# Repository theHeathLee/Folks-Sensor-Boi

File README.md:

# Folks Sensor Boi

> Multi-sensor engine telemetry unit for gasoline vehicles. Collects six engine parameters and transmits them wirelessly to a companion app and over CAN bus.

---

## Overview

A compact, sealed sensor interface box designed to mount in the engine bay of a classic or modified gasoline vehicle. Built around the ESP32-WROOM-S3.

Designed for JLCPCB fabrication and SMT assembly. 

---

## Features

| Channel | Sensor / method | Interface |
|---|---|---|
| Exhaust / CHT temperature | K-type thermocouple (galvanically isolated) | SPI — MAX31856 |
| Engine RPM | Ignition coil primary (optocoupled) | GPIO interrupt |
| Wheel speed | Hall effect sensor + Schmitt trigger | GPIO interrupt |
| Oil temperature | NTC sender (VDO-type) | ADC |
| Manifold vacuum / MAP | MPXHZ6115A6T1 15–115 kPa | ADC |
| Battery voltage | Resistor divider | ADC |

**Outputs**
- WiFi 802.11 b/g/n (AP mode) + BLE 4.2 → companion app
- CAN 2.0B @ 500 kbit/s via SN65HVD230

**Programming**
- USB-C (CP2102N) with auto-reset circuit — no manual BOOT/EN required

---

## Schematic

<!-- schematic-start -->

<!-- schematic-end -->

---

## Hardware

### MCU
- **ESP32-WROOM-32U-N4** — dual-core 240 MHz, WiFi, BLE, TWAI CAN, SPI, 12-bit ADC
- External u.FL antenna for full-vehicle wireless range

---
)

```
├── hardware/
│   ├── engine-sensor-box.kicad_pro
│   ├── engine-sensor-box.kicad_sch
│   ├── engine-sensor-box.kicad_pcb
│   ├── sym-lib-table
│   ├── fp-lib-table
│   └── jlcimport/               # project-local imported symbols + footprints
├── production/
│   ├── gerbers/
│   ├── bom.csv                  # JLCPCB-format BOM
│   └── positions.csv            # CPL file
├── docs/
│   └── engine_sensor_box_BOM.xlsx
└── README.md
```

---

## BOM

<!-- bom-start -->

[Open interactive BOM →](https://theheathlee.github.io/Folks-Sensor-Boi/bom.html)
<!-- bom-end -->

Full BOM with LCSC part numbers, stock status, unit costs, and placement tracking is in [`engine_sensor_box_BOM.xlsx`](engine_sensor_box_BOM.xlsx).

---

## Firmware

> Firmware repository: _link TBD_

---

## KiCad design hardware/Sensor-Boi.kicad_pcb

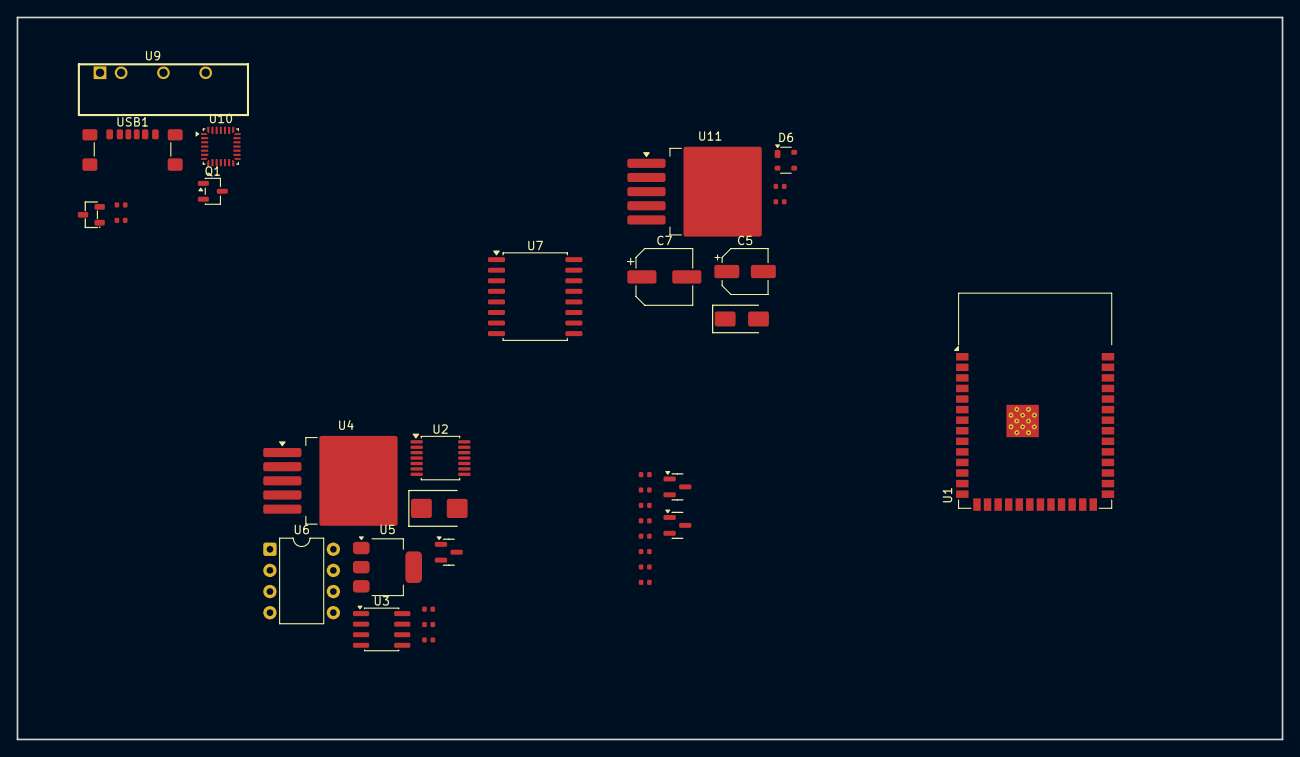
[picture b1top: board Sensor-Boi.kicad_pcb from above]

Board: 2 copper layers, 152.0 x 86.8 mm, 36 parts (0 on the bottom side), 19 nets, no tracks yet.

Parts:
C1, C2, C3, C4, C6: 100nF; C_0402
C5: 47uF 16V; CP_Elec_5x5.4
C7: 100uF 50V; CP_Elec_6.3x7.7
D1: BZX84C5V1; D_SOT-23
D2: SMBJ15A; D_SMB
D2#2: SS34; D_SMA
D3, D4: BZX84C3V3; D_SOT-23
D6: PRTR5V0U2X; SOT-143
Q1: 2N7002; SOT-23-3
R1: 100kΩ; R_0402
R2: 470Ω; R_0402
R3: 120Ω; R_0402
R4: 5.1kΩ; R_0402
R5, R10: 100Ω; R_0402
R6, R8: 10kΩ; R_0402
R7: 15kΩ; R_0402
R9: 180Ω; R_0402
U1: ESP32-S3-WROOM-1
U2: MAX31856; TSSOP-14_4.4x5mm_P0.65mm
U3: SN65HVD230; SOIC-8_3.9x4.9mm_P1.27mm
U4: LM2596S-5; TO-263-5_TabPin3
U5: AMS1117-3.3; SOT-223-3_TabPin2
U6: 6N137; DIP-8_W7.62mm
U7: ISO7741DWR; SOIC-16W_7.5x10.3mm_P1.27mm
U8: LTC4412ES6_TRPBF; SOT-23-3_L2.9-W1.3-P0.95-LS2.4-BR
U9: B0505LS-1WR3_C7465180
U10: CP2102N-A02-GQFN24R; QFN-28_4x4mm_P0.5mm
U11: LM2596S-3.3; TO-263-5_TabPin3
USB1: USB4085-GF-A_C7095263; USB_C_Receptacle_GCT_USB4135-GF-A_6P_TopMnt_Horizontal

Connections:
/3V3: C5.1, D6.4 (VCC), R9.2, U1.2 (3V3), U3.3 (VCC), U5.2 (VO), U7.16 (VCC2), U9.1 (VIN), U11.4 (FB)
/3V3_Isolated: U2.5 (AVDD), U2.8 (DVDD), U7.1 (VCC1), U9.6 (+Vo)
/12V: C7.1, U11.1 (VIN)
/CAN_H: R3.1, U3.7 (CANH)
/CAN_L: R3.2, U3.6 (CANL)
/CAN_RX: U1.10 (IO17), U3.4 (R)
/CAN_TX: U1.11 (IO18), U3.1 (D)
/Hall_Sensor: C6.1, R10.1
/Lambda_MCU: C2.1, D3.1, R6.2, R7.1, U1.6 (IO6)
/MAP_Signal_MCU: C3.1, D4.1, R8.2, U1.39 (IO1)
/OIL_MCU: C4.1, R9.1, U1.38 (IO2)
/TEMP_SCK: U2.10 (SCK), U7.3 (INA)
/TEMP_SDI: U2.12 (SDI), U7.5 (INC)
/TEMP_SDO: U2.11 (SDO), U7.4 (INB)
GND: C2.2, C3.2, C4.2, C5.2, C7.2, D2#2.1, D4.3, D6.1 (GND), R7.2, U1.1 (GND), U1.40 (GND), U1.41 (GND), U3.2 (GND), U4.3 (GND_3), U5.1 (GND), U7.15 (GND2), U8.2 (GND_2), U9.2 (GND), U11.3 (GND), U11.5 (~ON/OFF)
GND2: U2.1 (AGND), U2.14 (DGND), U7.2 (GND1), U9.4 (0V)
unnamed: D6.2 (I/O1), R10.2
unnamed: R5.2, R6.1
unnamed: D2#2.2, U11.2 (OUT)

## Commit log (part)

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2026-05-24 add a majority of symbols to schematic
2026-05-24 add readme
2026-05-24 Rename project from 'Engine Sensor Box' to 'Folks Sensor Boi'
2026-05-24 Add CERN Open Hardware Licence Version 2
    Added CERN Open Hardware Licence Version 2 - Strongly Reciprocal to the project.
2026-05-24 add gh action for doc generation
2026-05-24 ci: regenerate schematic and BOM [skip ci]
2026-05-24 add outline to pcb
2026-06-23 add some connections
2026-06-23 add power electronics and connections
